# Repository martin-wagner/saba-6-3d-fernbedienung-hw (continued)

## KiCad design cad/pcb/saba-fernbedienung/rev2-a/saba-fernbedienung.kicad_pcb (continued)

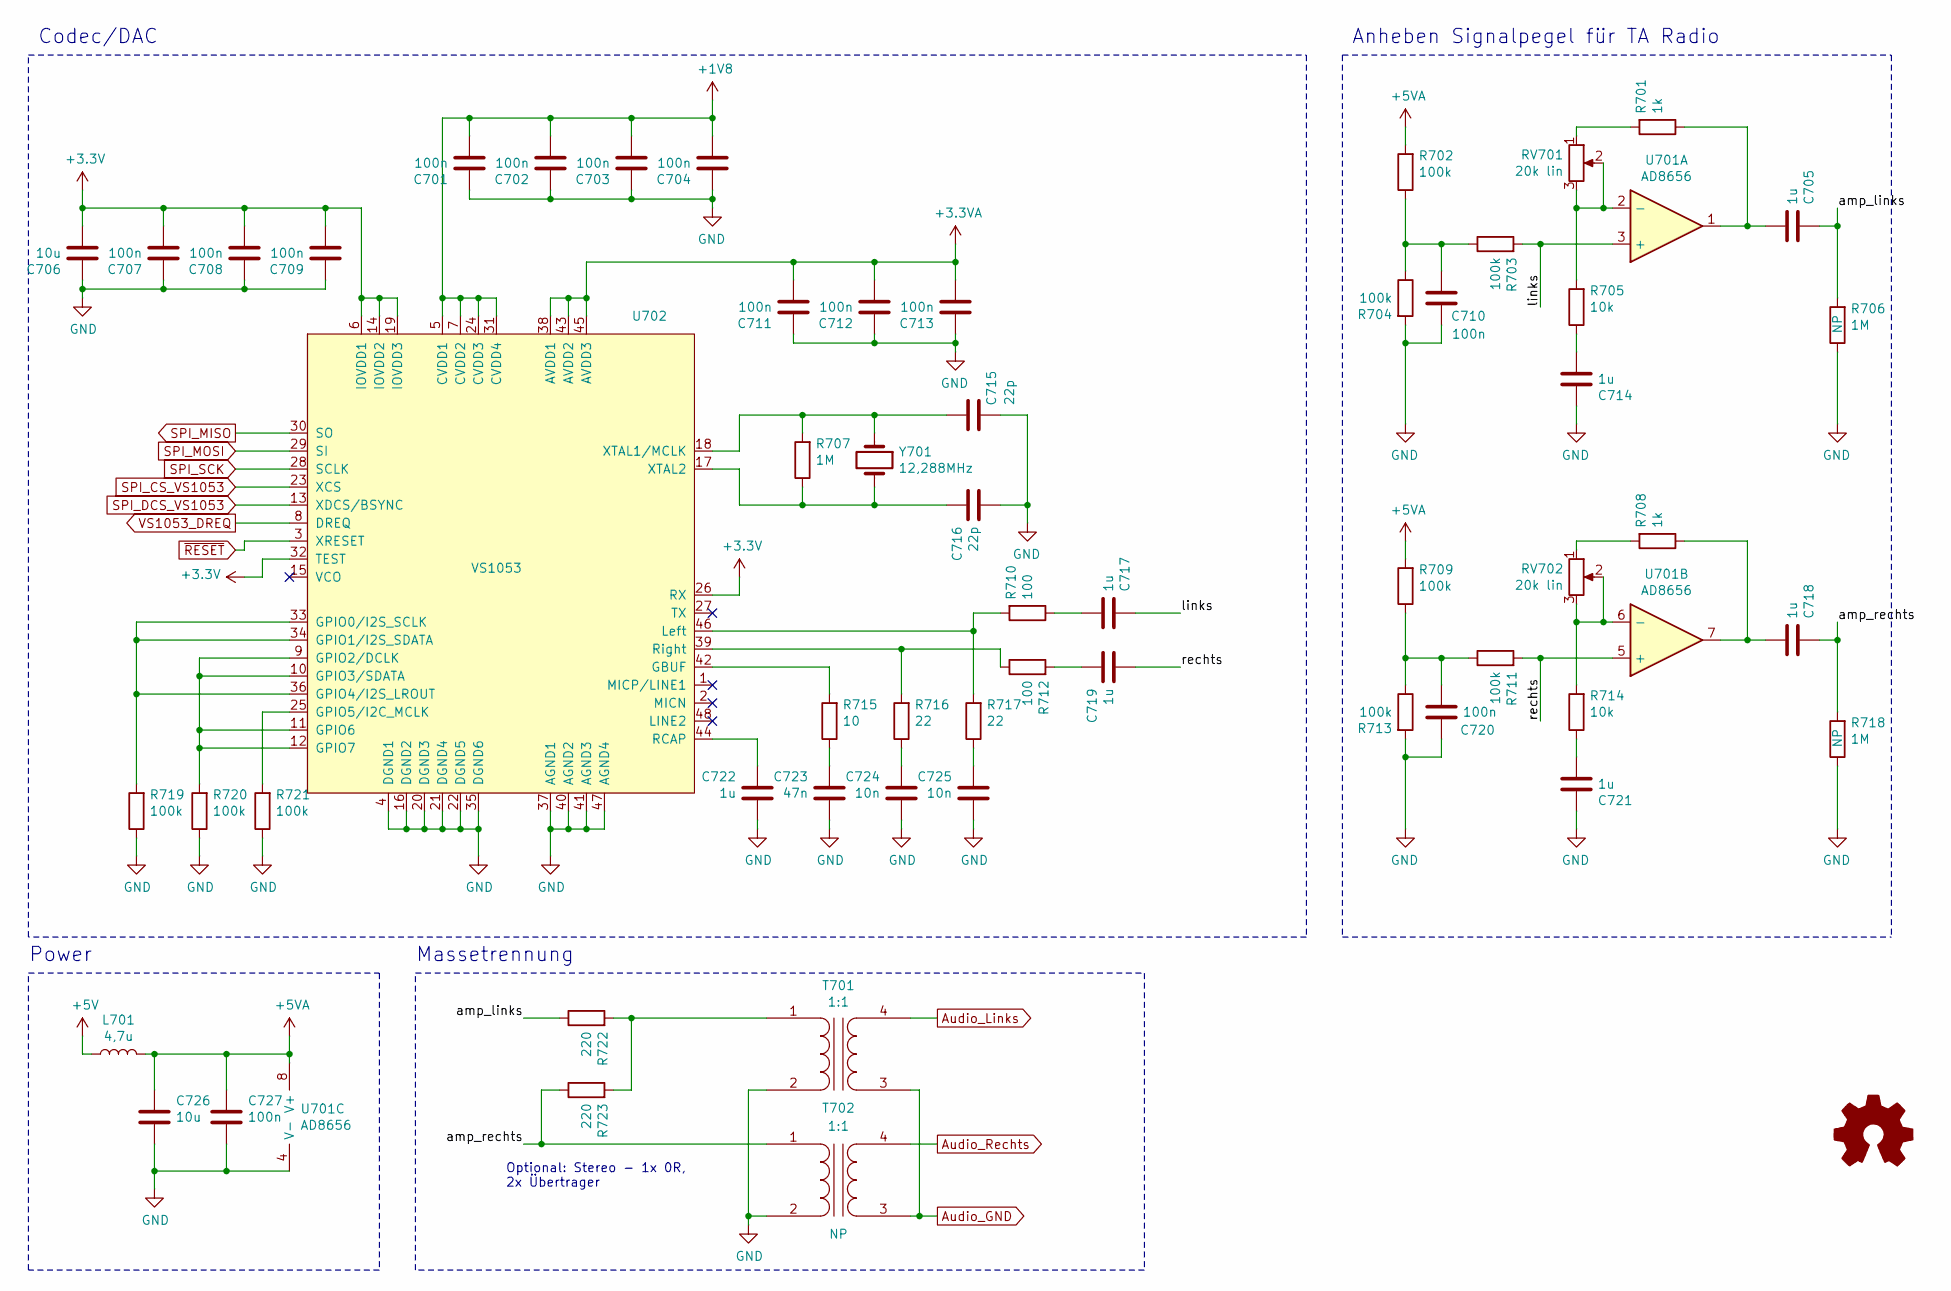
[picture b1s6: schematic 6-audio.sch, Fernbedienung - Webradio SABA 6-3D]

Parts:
C701, C702, C703, C704, C707, C708, C709, C710, C711, C712, C713, C720, C727: 100n; C_0603_1608Metric
C705, C714, C717, C718, C719, C721, C722: 1u; C_0805_2012Metric
C706, C726: 10u; C_1206_3216Metric
C715, C716: 22p; C_0603_1608Metric
C723: 47n; C_0603_1608Metric
C724, C725: 10n; C_0603_1608Metric
L701: 4,7u; WE-LQ
R701, R708: 1k; R_0603_1608Metric
R702, R703, R704, R709, R711, R713, R719, R720, R721: 100k; R_0603_1608Metric
R705, R714: 10k; R_0603_1608Metric
R706, R707, R718: 1M; R_0603_1608Metric
R710, R712: 100; R_0603_1608Metric
R715: 10; R_0603_1608Metric
R716, R717: 22; R_0603_1608Metric
R722, R723: 220; R_0603_1608Metric
RV701, RV702: 20k lin; Potentiometer_Vishay_TS53YL_Vertical
T701, T702: 1:1; Transformer_NF_EI14
U701: AD8656; SOIC-8_3.9x4.9mm_P1.27mm
U702: VS1053; LQFP-48_7x7mm_P0.5mm
Y701: 12,288MHz; Crystal_SMD_HC49-SD

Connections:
+1V8: C701.2, C702.2, C703.2, C704.2, U702.5 (CVDD1), U702.7 (CVDD2), U702.24 (CVDD3), U702.31 (CVDD4); also elsewhere on the board
+3.3VA: C711.2, C712.2, C713.2, U702.38 (AVDD1), U702.43 (AVDD2), U702.45 (AVDD3); also elsewhere on the board
+5V: L701.1; also elsewhere on the board
+5VA: C726.1, C727.1, L701.2, R702.2, R709.2, U701.8 (V+)
/Audio/amp_links: C705.1, R706.2, R722.1
/Audio/amp_rechts: C718.1, R718.2, R723.1, T702.1 (AA)
/Audio/links: C717.1, R703.2, U701.3 (+)
/Audio/rechts: C719.2, R711.2, U701.5 (+)
Audio_GND: T701.3 (SA), T702.3 (SA); also elsewhere on the board
Audio_Links: T701.4 (SB); also elsewhere on the board
Audio_Rechts: T702.4 (SB); also elsewhere on the board
GND: C701.1, C702.1, C703.1, C704.1, C706.1, C707.1, C708.1, C709.1, C710.1, C711.1, C712.1, C713.1, C714.1, C715.2, C716.2, C720.2, C721.1, C722.2, C723.2, C724.2, C725.2, C726.2, C727.2, R704.2, R706.1, R713.2, R718.1, R719.1, R720.1, R721.1, T701.2 (AB), T702.2 (AB), U701.4 (V-), U702.4 (DGND1), U702.16 (DGND2), U702.20 (DGND3), U702.21 (DGND4), U702.22 (DGND5), U702.35 (DGND6), U702.37 (AGND1), U702.40 (AGND2), U702.41 (AGND3), U702.47 (AGND4); also elsewhere on the board
unnamed: C705.2, R701.1, U701.1
unnamed: C710.2, R702.1, R703.1, R704.1
unnamed: C714.2, R705.1
unnamed: C715.1, R707.2, U702.18 (XTAL1/MCLK), Y701.1
unnamed: C716.1, R707.1, U702.17 (XTAL2), Y701.2
unnamed: C717.2, R710.1
unnamed: C718.2, R708.1, U701.7
unnamed: C719.1, R712.2
unnamed: C720.1, R709.1, R711.1, R713.1
unnamed: C721.2, R714.1
unnamed: C722.1, U702.44 (RCAP)
unnamed: C723.1, R715.1
unnamed: C724.1, R716.1
unnamed: C725.1, R717.1
unnamed: R701.2, RV701.1
unnamed: R705.2, RV701.2, RV701.3, U701.2 (-)
unnamed: R708.2, RV702.1
unnamed: R710.2, R717.2, U702.46 (Left)
unnamed: R712.1, R716.2, U702.39 (Right)
unnamed: R714.2, RV702.2, RV702.3, U701.6 (-)
unnamed: R715.2, U702.42 (GBUF)
unnamed: R719.2, U702.33 (GPIO0/I2S_SCLK), U702.34 (GPIO1/I2S_SDATA), U702.36 (GPIO4/I2S_LROUT)
unnamed: R720.2, U702.9 (GPIO2/DCLK), U702.10 (GPIO3/SDATA), U702.11 (GPIO6), U702.12 (GPIO7)
unnamed: R721.2, U702.25 (GPIO5/I2C_MCLK)
unnamed: R722.2, R723.2, T701.1 (AA)
SPI_CS_VS1053: U702.23 (XCS); also elsewhere on the board
SPI_DCS_VS1053: U702.13 (XDCS/BSYNC); also elsewhere on the board
SPI_MISO: U702.30 (SO); also elsewhere on the board
SPI_MOSI: U702.29 (SI); also elsewhere on the board
SPI_SCK: U702.28 (SCLK); also elsewhere on the board
VS1053_DREQ: U702.8 (DREQ); also elsewhere on the board
~RESET: U702.3 (XRESET); also elsewhere on the board

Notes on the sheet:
Codec/DAC
Anheben Signalpegel für TA Radio
Power
Massetrennung
Optional: Stereo - 1x 0R, 2x Übertrager

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
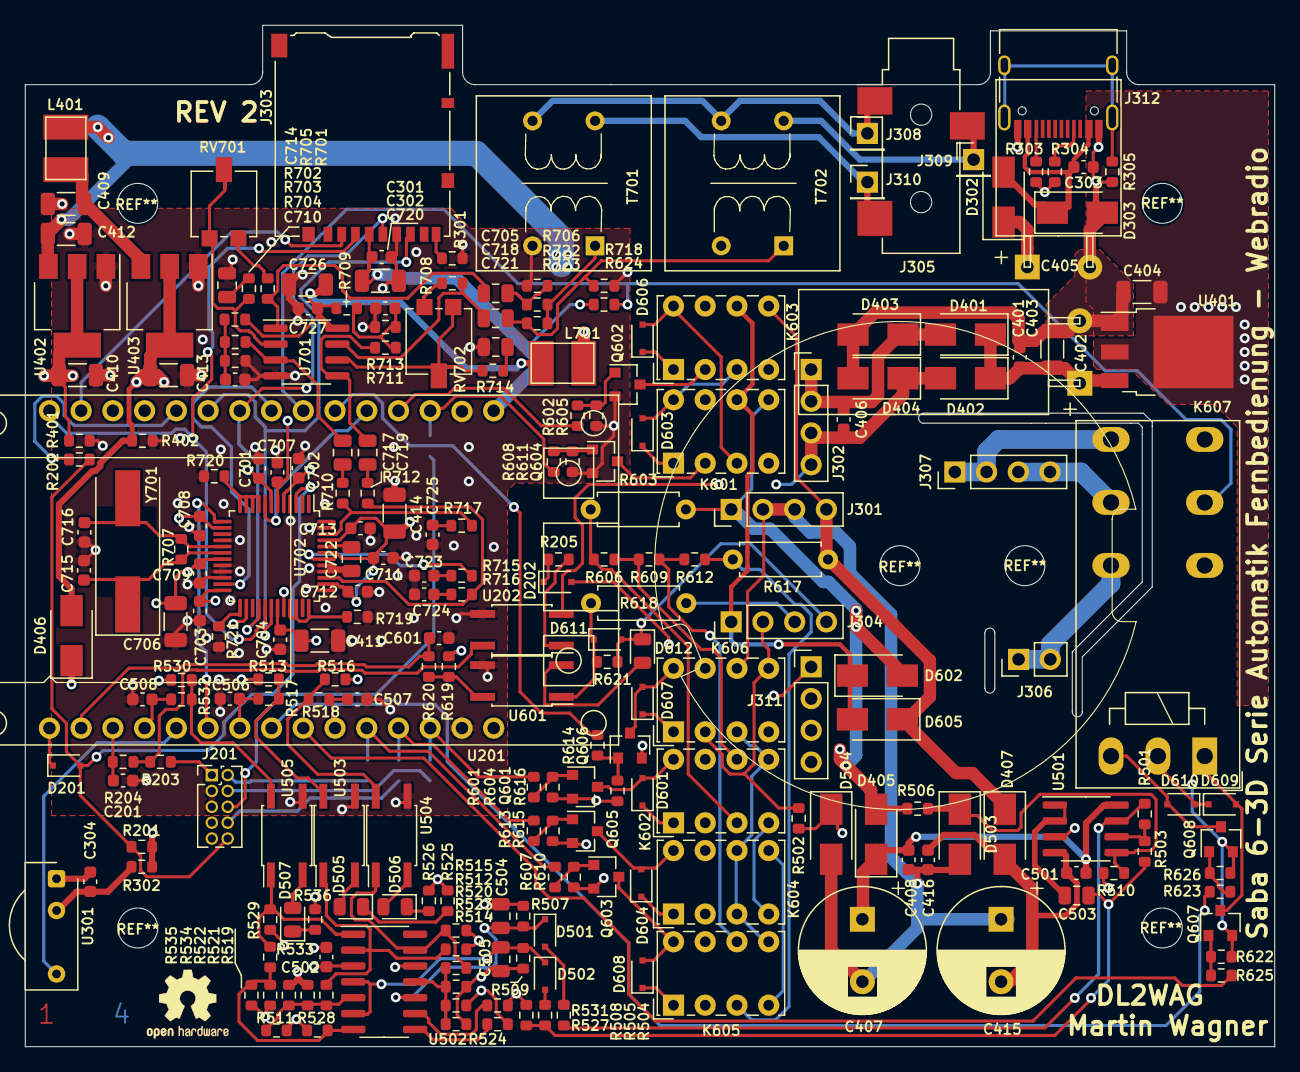
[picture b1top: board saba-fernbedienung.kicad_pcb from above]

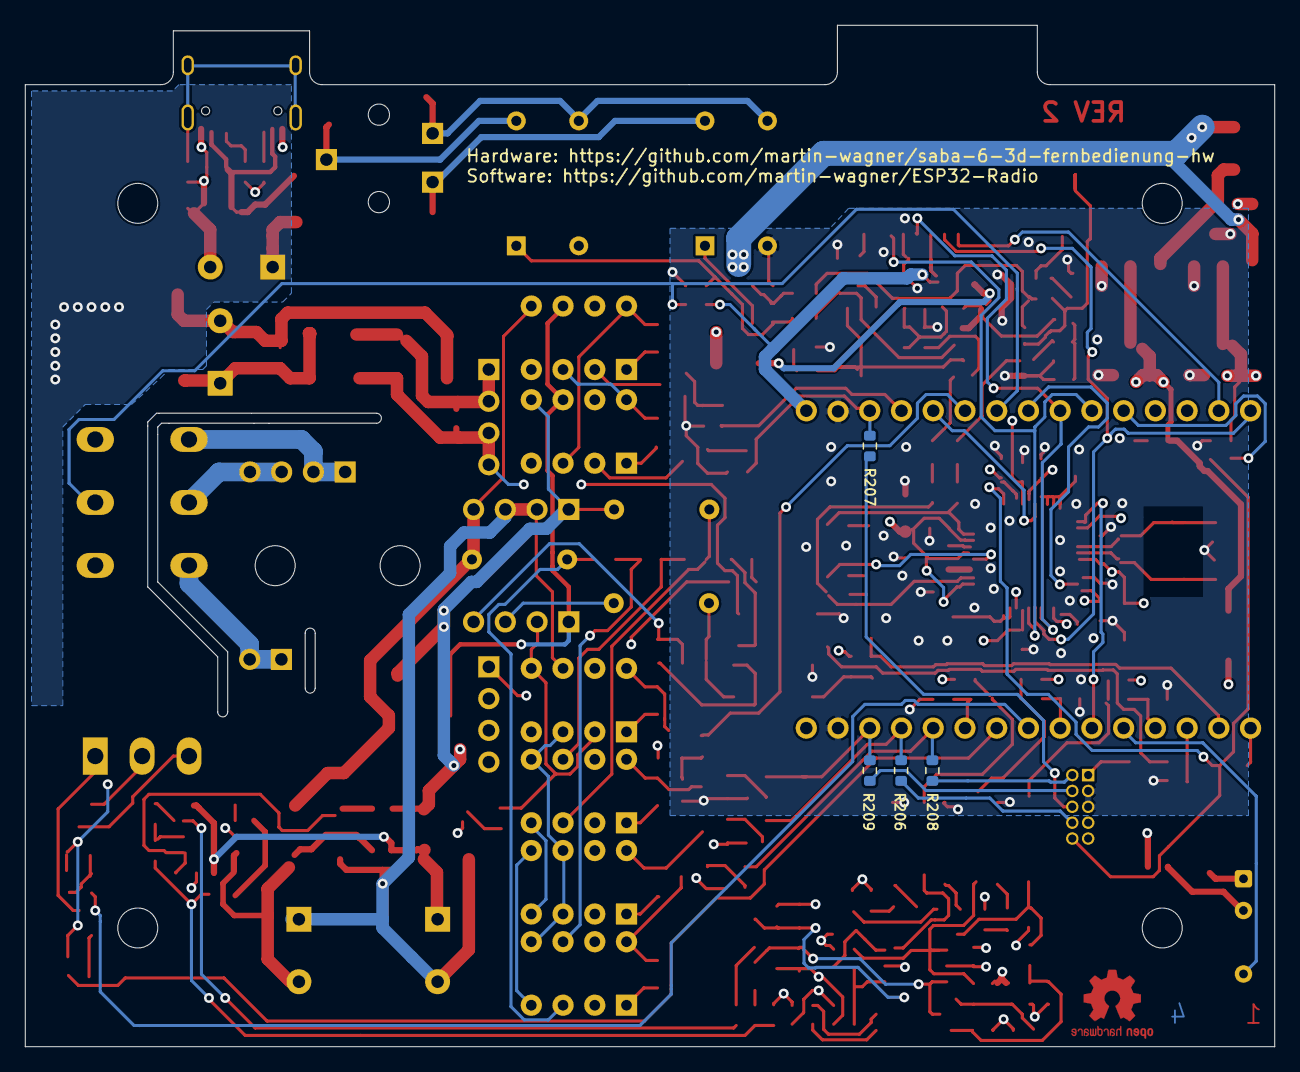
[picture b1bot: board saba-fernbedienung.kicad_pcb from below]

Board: 4 copper layers, 100.0 x 81.8 mm, 237 parts (4 on the bottom side), 148 nets.

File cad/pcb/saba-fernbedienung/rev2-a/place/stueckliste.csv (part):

"Source:","/home/martin/elektronik/radios/saba fernbedienung/cad/pcb/saba-fernbedienung/rev2-a/saba-fernbedienung.sch"
"Date:","Wed 18 Aug 2021 13:08:03 CEST"
"Tool:","Eeschema 5.1.10-88a1d61d58~88~ubuntu18.04.1"
"Generator:","/usr/share/kicad/plugins/bom_csv_grouped_by_value.py"
"Component Count:","237"

"Individual Components:"

"Item","Qty","Reference(s)","Value","LibPart","Footprint","Datasheet","Bauteil","Coil Voltage","Placement","Voltage"
"","","C201","100n","Device:C","Capacitor_SMD:C_0603_1608Metric","~","WE 885382206004","","",""
"","","C301","100n","Device:C","Capacitor_SMD:C_0603_1608Metric","~","WE 885382206004","","",""
"","","C302","10u","Device:C","Capacitor_SMD:C_1206_3216Metric","~","WE 885012208069","","",""
"","","C303","100n","Device:C","Capacitor_SMD:C_0603_1608Metric","~","WE 885382206004","","NP",""
"","","C304","100n","Device:C","Capacitor_SMD:C_0603_1608Metric","~","WE 885382206004","","",""
"","","C401","100n","Device:C","Capacitor_SMD:C_0603_1608Metric","~","WE 885382206004","","",""
"","","C402","1000u","Device:CP","local:CP_Radial_D10.0mm_P5.00mm_L20.00mm_liegend","~","WE 860020375017","","","16V"
"","","C403","10u","Device:C","Capacitor_SMD:C_1206_3216Metric","~","WE 885012208069","","",""
"","","C404","10u","Device:C","Capacitor_SMD:C_1206_3216Metric","~","WE 885012208069","","",""
"","","C405","220u","Device:CP","local:CP_Radial_D10.0mm_P5.00mm_L12.50mm_liegend","~","WE 860020675020","","","10V"
"","","C406","100n","Device:C","Capacitor_SMD:C_0603_1608Metric","~","WE 885382206004","","",""
"","","C407","220u","Device:CP","Capacitor_THT:CP_Radial_D10.0mm_P5.00mm","~","WE 860020675020","","","50V"
"","","C408","100n","Device:C","Capacitor_SMD:C_0603_1608Metric","~","WE 885382206004","","",""
"","","C409","10u","Device:C","Capacitor_SMD:C_1206_3216Metric","~","WE 885012208069","","",""
"","","C410","10u","Device:C","Capacitor_SMD:C_1206_3216Metric","~","WE 885012208069","","",""
"","","C411","10u","Device:C","Capacitor_SMD:C_1206_3216Metric","~","WE 885012208069","","",""
"","","C412","10u","Device:C","Capacitor_SMD:C_1206_3216Metric","~","WE 885012208069","","",""
"","","C413","10u","Device:C","Capacitor_SMD:C_1206_3216Metric","~","WE 885012208069","","",""
"","","C414","10u","Device:C","Capacitor_SMD:C_1206_3216Metric","~","WE 885012208069","","",""
"","","C415","220u","Device:CP","Capacitor_THT:CP_Radial_D10.0mm_P5.00mm","~","WE 860020675020","","","50V"
"","","C416","100n","Device:C","Capacitor_SMD:C_0603_1608Metric","~","WE 885382206004","","",""
"","","C501","100n","Device:C","Capacitor_SMD:C_0603_1608Metric","~","WE 885382206004","","",""
"","","C502","100n","Device:C","Capacitor_SMD:C_0603_1608Metric","~","WE 885382206004","","",""
"","","C503","470n","Device:C","Capacitor_SMD:C_0805_2012Metric","~","WE 885012207102","","",""
"","","C504","470n","Device:C","Capacitor_SMD:C_0805_2012Metric","~","WE 885012207102","","",""
"","","C505","470n","Device:C","Capacitor_SMD:C_0805_2012Metric","~","WE 885012207102","","",""
"","","C506","100n","Device:C","Capacitor_SMD:C_0603_1608Metric","~","WE 885382206004","","",""
"","","C507","100n","Device:C","Capacitor_SMD:C_0603_1608Metric","~","WE 885382206004","","",""
"","","C508","100n","Device:C","Capacitor_SMD:C_0603_1608Metric","~","WE 885382206004","","",""
"","","C601","100n","Device:C","Capacitor_SMD:C_0603_1608Metric","~","WE 885382206004","","",""
"","","C701","100n","Device:C","Capacitor_SMD:C_0603_1608Metric","~","WE 885382206004","","",""
"","","C702","100n","Device:C","Capacitor_SMD:C_0603_1608Metric","~","WE 885382206004","","",""
"","","C703","100n","Device:C","Capacitor_SMD:C_0603_1608Metric","~","WE 885382206004","","",""
"","","C704","100n","Device:C","Capacitor_SMD:C_0603_1608Metric","~","WE 885382206004","","",""
"","","C705","1u","Device:C","Capacitor_SMD:C_0805_2012Metric","~","WE 885012207078","","",""
"","","C706","10u","Device:C","Capacitor_SMD:C_1206_3216Metric","~","WE 885012208069","","",""
"","","C707","100n","Device:C","Capacitor_SMD:C_0603_1608Metric","~","WE 885382206004","","",""
"","","C708","100n","Device:C","Capacitor_SMD:C_0603_1608Metric","~","WE 885382206004","","",""
"","","C709","100n","Device:C","Capacitor_SMD:C_0603_1608Metric","~","WE 885382206004","","",""
"","","C710","100n","Device:C","Capacitor_SMD:C_0603_1608Metric","~","WE 885382206004","","",""
"","","C711","100n","Device:C","Capacitor_SMD:C_0603_1608Metric","~","WE 885382206004","","",""
"","","C712","100n","Device:C","Capacitor_SMD:C_0603_1608Metric","~","WE 885382206004","","",""
"","","C713","100n","Device:C","Capacitor_SMD:C_0603_1608Metric","~","WE 885382206004","","",""
"","","C714","1u","Device:C","Capacitor_SMD:C_0805_2012Metric","~","WE 885012207078","","",""
"","","C715","22p","Device:C","Capacitor_SMD:C_0603_1608Metric","~","WE 885012206079","","",""
"","","C716","22p","Device:C","Capacitor_SMD:C_0603_1608Metric","~","WE 885012206079","","",""
"","","C717","1u","Device:C","Capacitor_SMD:C_0805_2012Metric","~","WE 885012207078","","",""
"","","C718","1u","Device:C","Capacitor_SMD:C_0805_2012Metric","~","WE 885012207078","","",""
"","","C719","1u","Device:C","Capacitor_SMD:C_0805_2012Metric","~","WE 885012207078","","",""
"","","C720","100n","Device:C","Capacitor_SMD:C_0603_1608Metric","~","WE 885382206004","","",""
"","","C721","1u","Device:C","Capacitor_SMD:C_0805_2012Metric","~","WE 885012207078","","",""
"","","C722","1u","Device:C","Capacitor_SMD:C_0805_2012Metric","~","WE 885012207078","","",""
"","","C723","47n","Device:C","Capacitor_SMD:C_0603_1608Metric","~","WE 885012206093","","",""
"","","C724","10n","Device:C","Capacitor_SMD:C_0603_1608Metric","~","WE 885012206089","","",""
"","","C725","10n","Device:C","Capacitor_SMD:C_0603_1608Metric","~","WE 885012206089","","",""
"","","C726","10u","Device:C","Capacitor_SMD:C_1206_3216Metric","~","WE 885012208069","","",""
"","","C727","100n","Device:C","Capacitor_SMD:C_0603_1608Metric","~","WE 885382206004","","",""
"","","D201","1N4148","Device:D","Diode_SMD:D_SOD-323F","~","0R","","",""
"","","D202","1N4148","Device:D","Diode_SMD:D_SOD-323F","~","ON 1N4148WS","","",""
"","","D302","B140-E3","Diode:B140-E3","Diode_SMD:D_SMA","http://www.vishay.com/docs/88946/b120.pdf","Vishay B140-E3/61T","","NP",""
"","","D303","SMAJ5.0A","Diode:SM6T6V8A","Diode_SMD:D_SMA","","SMAJ5.0A-13-F","","NP",""
"","","D401","B140-E3","Diode:B140-E3","Diode_SMD:D_SMA","http://www.vishay.com/docs/88946/b120.pdf","Vishay B140-E3/61T","","",""
"","","D402","B140-E3","Diode:B140-E3","Diode_SMD:D_SMA","http://www.vishay.com/docs/88946/b120.pdf","Vishay B140-E3/61T","","",""
"","","D403","B140-E3","Diode:B140-E3","Diode_SMD:D_SMA","http://www.vishay.com/docs/88946/b120.pdf","Vishay B140-E3/61T","","",""
"","","D404","B140-E3","Diode:B140-E3","Diode_SMD:D_SMA","http://www.vishay.com/docs/88946/b120.pdf","Vishay B140-E3/61T","","",""
"","","D405","1N4007","Device:D","Diode_SMD:D_SMA","~","1N4007FLTR","","",""
"","","D406","B140-E3","Diode:B140-E3","Diode_SMD:D_SMA","http://www.vishay.com/docs/88946/b120.pdf","Vishay B140-E3/61T","","",""
"","","D407","1N4007","Device:D","Diode_SMD:D_SMA","~","1N4007FLTR","","",""
"","","D501","1N4148","Device:D","Diode_SMD:D_SOD-323F","~","ON 1N4148WS","","",""
"","","D502","1N4148","Device:D","Diode_SMD:D_SOD-323F","~","ON 1N4148WS","","",""
"","","D503","SMAJ33CA","Device:D_TVS","Diode_SMD:D_SMA","~","Diodes SMAJ33CAQ-13-F","","",""
"","","D504","SMAJ33CA","Device:D_TVS","Diode_SMD:D_SMA","~","Diodes SMAJ33CAQ-13-F","","",""
"","","D505","LED","Device:LED","LED_SMD:LED_0805_2012Metric","~","WE 150080BS75000","","",""
"","","D506","LED","Device:LED","LED_SMD:LED_0805_2012Metric","~","WE 150080BS75000","","",""
"","","D507","LED","Device:LED","LED_SMD:LED_0805_2012Metric","~","WE 150080BS75000","","",""
"","","D601","1N4148","Device:D","Diode_SMD:D_SOD-323F","~","ON 1N4148WS","","",""
"","","D602","SMAJ33CA","Device:D_TVS","Diode_SMD:D_SMA","~","Diodes SMAJ33CAQ-13-F","","",""
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
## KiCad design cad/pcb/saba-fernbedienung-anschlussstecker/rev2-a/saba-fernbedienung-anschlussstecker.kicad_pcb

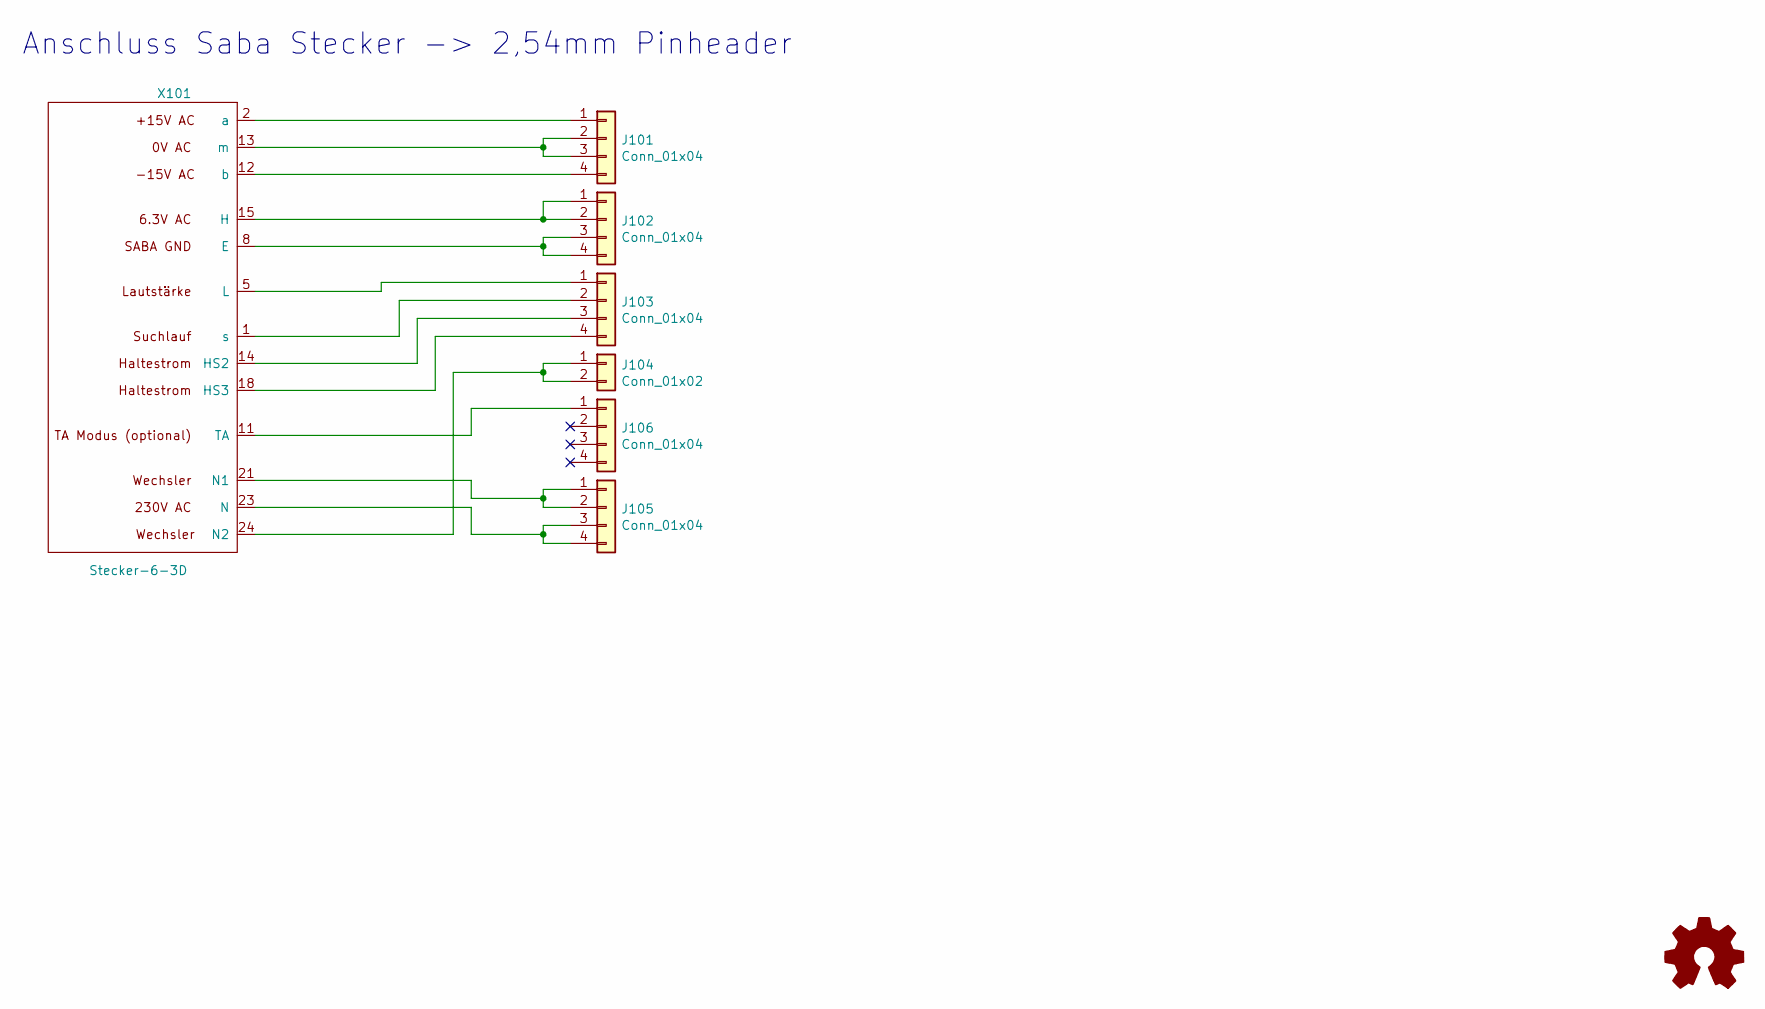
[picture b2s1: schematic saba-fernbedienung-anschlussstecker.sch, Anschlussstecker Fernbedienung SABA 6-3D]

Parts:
J101, J102, J103, J105, J106: Conn_01x04; PinHeader_1x04_P2.54mm_Vertical
J104: Conn_01x02; PinHeader_1x02_P2.54mm_Vertical
X101: Stecker-6-3D; stecker-6-3d

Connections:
unnamed: J101.1, X101.2 (a)
unnamed: J101.2, J101.3, X101.13 (m)
unnamed: J101.4, X101.12 (b)
unnamed: J102.1, J102.2, X101.15 (H)
unnamed: J102.3, J102.4, X101.8 (E)
unnamed: J103.1, X101.5 (L)
unnamed: J103.2, X101.1 (s)
unnamed: J103.3, X101.14 (HS2)
unnamed: J103.4, X101.18 (HS3)
unnamed: J104.1, J104.2, X101.24 (N2)
unnamed: J105.1, J105.2, X101.21 (N1)
unnamed: J105.3, J105.4, X101.23 (N)
unnamed: J106.1, X101.11 (TA)

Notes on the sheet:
Anschluss Saba Stecker -> 2,54mm Pinheader

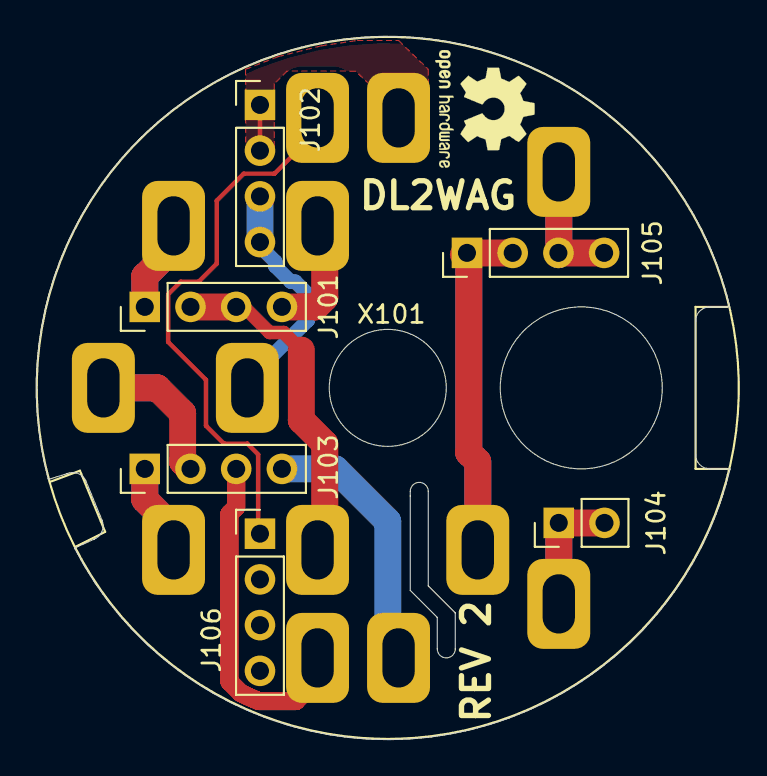
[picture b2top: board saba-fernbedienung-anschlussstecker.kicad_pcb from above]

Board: 2 copper layers, 38.5 x 39.1 mm, 7 parts (0 on the bottom side), 13 nets.

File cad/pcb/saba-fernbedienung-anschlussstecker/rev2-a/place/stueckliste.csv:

"Source:","/home/martin/elektronik/radios/saba fernbedienung/cad/pcb/saba-fernbedienung-anschlussstecker/rev2-a/saba-fernbedienung-anschlussstecker.sch"
"Date:","Mon 08 Aug 2022 17:44:44 CEST"
"Tool:","Eeschema 5.1.12-84ad8e8a86~92~ubuntu20.04.1"
"Generator:","/usr/share/kicad/plugins/bom_csv_grouped_by_value.py"
"Component Count:","7"

"Individual Components:"

"Item","Qty","Reference(s)","Value","LibPart","Footprint","Datasheet"
"","","J101","Conn_01x04","Connector_Generic:Conn_01x04","Connector_PinHeader_2.54mm:PinHeader_1x04_P2.54mm_Vertical","~"
"","","J102","Conn_01x04","Connector_Generic:Conn_01x04","Connector_PinHeader_2.54mm:PinHeader_1x04_P2.54mm_Vertical","~"
"","","J103","Conn_01x04","Connector_Generic:Conn_01x04","Connector_PinHeader_2.54mm:PinHeader_1x04_P2.54mm_Vertical","~"
"","","J104","Conn_01x02","Connector_Generic:Conn_01x02","Connector_PinHeader_2.54mm:PinHeader_1x02_P2.54mm_Vertical","~"
"","","J105","Conn_01x04","Connector_Generic:Conn_01x04","Connector_PinHeader_2.54mm:PinHeader_1x04_P2.54mm_Vertical","~"
"","","J106","Conn_01x04","Connector_Generic:Conn_01x04","Connector_PinHeader_2.54mm:PinHeader_1x04_P2.54mm_Vertical","~"
"","","X101","Stecker-6-3D","stecker:Stecker-6-3D","stecker:stecker-6-3d",""



"Collated Components:"

"Item","Qty","Reference(s)","Value","LibPart","Footprint","Datasheet"
"1","5","J101, J102, J103, J105, J106","Conn_01x04","Connector_Generic:Conn_01x04","Connector_PinHeader_2.54mm:PinHeader_1x04_P2.54mm_Vertical","~"
"2","1","J104","Conn_01x02","Connector_Generic:Conn_01x02","Connector_PinHeader_2.54mm:PinHeader_1x02_P2.54mm_Vertical","~"
"3","1","X101","Stecker-6-3D","stecker:Stecker-6-3D","stecker:stecker-6-3d",""

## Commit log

2021-01-11 Initial Commit...
    Simulation hinzugefuegt
2021-01-11 New: Lizenz
2021-01-11 Add: Anschlussstecker
2021-01-11 Add: Controller
2021-01-13 Add: Steuerschaltung, Codec, Audio
2021-01-13 Fix: Div. DRC
2021-01-13 New: Bauteil - Pad Zuordnungen
2021-01-13 Fix: uC Gehaeuse
2021-01-13 Add: Bauteiltypen Digikey...
    viele Bauteile von WE da hoffentlich lange gueltig...
2021-01-14 Change: Relais SMT -> THT, Sicherung PCB
2021-01-14 Sicherung
2021-01-16 PCB: Alle Leitungen verlegt
2021-01-16 Fix: DRC Fehler
2021-01-16 Add: Position Bauteilnummern Druck
2021-01-16 Change: Position Steckerpins
2021-01-16 Fab Layer
2021-01-16 Add: Herstellungsdaten
2021-01-21 Fix: Opamp zweifach
2021-02-13 Add: Todo
2021-02-14 Add: weitere Todo
2021-04-10 Add: Doku
2021-04-10 Add: Doku Inbetriebnahme
2021-04-10 Change: Update Sim
2021-06-20 Add: Vermessen von div. Uebertragern...
    da DC/DC Wandler EMV bei Radioempfang FM deutlich hoerbar ist und ohne haben wir eine Masseschleife.
2021-08-14 New: Stecker rev2
    unveraendert aus rev1
2021-08-14 Fix: Stecker
    - Durchmesser Mittelloch groesser
    - Position Befestigungsloch weiter rechts
    - Position Pin15 korrigiert
    - Pin11 hinzugefuegt. Ist in der Steckdose nicht belegt.
2021-08-14 New: Controller V2
2021-08-14 ToDo-s bearbeitet
2021-08-14 Change: Bauteilbezeichner
2021-08-17 alle Bauteile platziert
2021-08-18 Controller Rev2 fertig
2021-08-18 Update div. Dateien
2022-06-05 Add: Testsoftware Arduino ESP32
2022-06-05 Update NP, Fix ToDo-s
2022-06-18 Update: Doku
2022-06-19 Update: Dok
2022-08-08 Add: Doku PDF
2022-08-08 Add: Firmware Binaries
2022-08-08 Fix: Markdown
2022-08-08 Fix: Nochmal Markdown
2022-08-08 remove redundant file
2022-08-08 Add: Gerbers
2024-01-11 Update: Doku Firmware compilieren mit PlatformIO
